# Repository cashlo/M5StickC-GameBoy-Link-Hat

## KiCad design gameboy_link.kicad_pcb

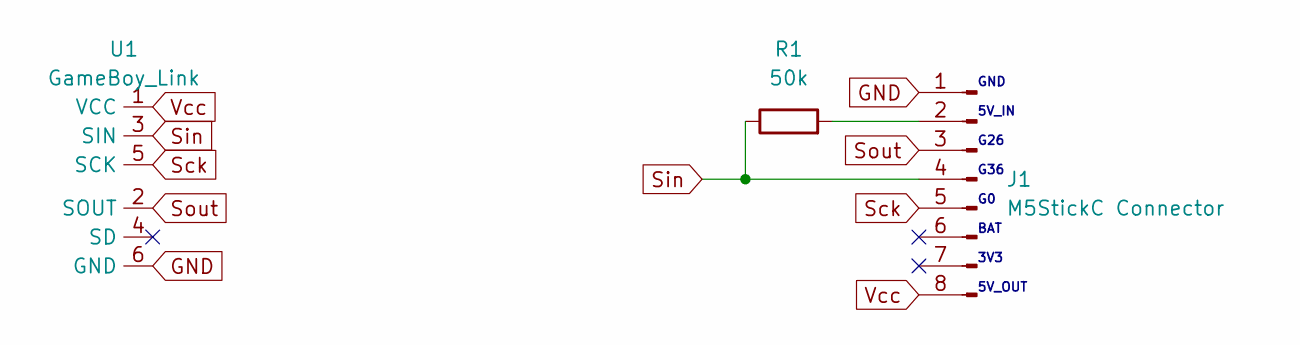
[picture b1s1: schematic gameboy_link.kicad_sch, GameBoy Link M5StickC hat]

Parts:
J1: M5StickC Connector; PinHeader_1x08_P2.54mm_Horizontal
R1: 50k; R_0805_2012Metric_Pad1.20x1.40mm_HandSolder
U1: GameBoy_Link; GameBoy_Link_Edge

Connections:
GND: J1.1, U1.6 (GND)
unnamed: J1.2, R1.2
Sck: J1.5, U1.5 (SCK)
Sin: J1.4, R1.1, U1.3 (SIN)
Sout: J1.3, U1.2 (SOUT)
Vcc: J1.8, U1.1 (VCC)

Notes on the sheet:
GND 5V_IN G26 G36 G0 BAT 3V3 5V_OUT

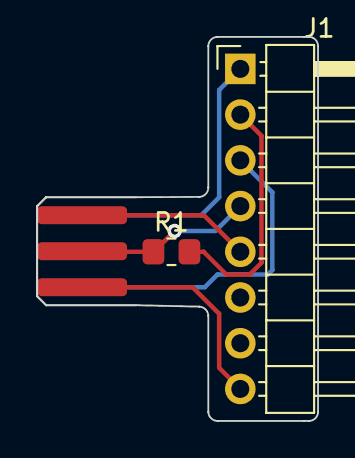
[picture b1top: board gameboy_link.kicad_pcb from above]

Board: 2 copper layers, 15.6 x 21.3 mm, 3 parts (0 on the bottom side), 6 nets.

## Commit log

2022-07-31 update desgin
